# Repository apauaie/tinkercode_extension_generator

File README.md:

**Use these files at your own risk.**

<br>

These files are generator files to create extension zip file for use with Tinkercode apps. It will generate a standard extension with same pin connection as Lekirbot. Please refer to the Lekirbot PCB. 
Content of this github is divided into two:
1. PCB Design with KICAD for LekirBot. It is a simple line following robot with 5 QRE1113 sensors, 2 servo connections, 1 ultrasonic connection, built in TB6612FNG Motor Driver
2. TinkerCode Block Extension Generator to be use with Tinkercode apps from tinkercode.my.

**Instruction to use PCB Files**
PCB files is for KICAD. Free to modify  (Open Source)
Download KICAD to modify these files. https://www.kicad.org/download/

)<br>

)<br>

)<br>

**Instruction to use Extension Generator Files**
Download the files from Github
Place GeneratorBot.exe and lekirbot folder in the same folder.

<br>

Run GeneratorBot.exe to generate extension zip file. Insert your Robot name and Robot Image.

<br>

In Tinkercode Apps, press the Extension (Spanar Icon) button to upload the zip files. 

)<br>

)<br>

Check if your upload is successful by going to the extension menu
)<br>

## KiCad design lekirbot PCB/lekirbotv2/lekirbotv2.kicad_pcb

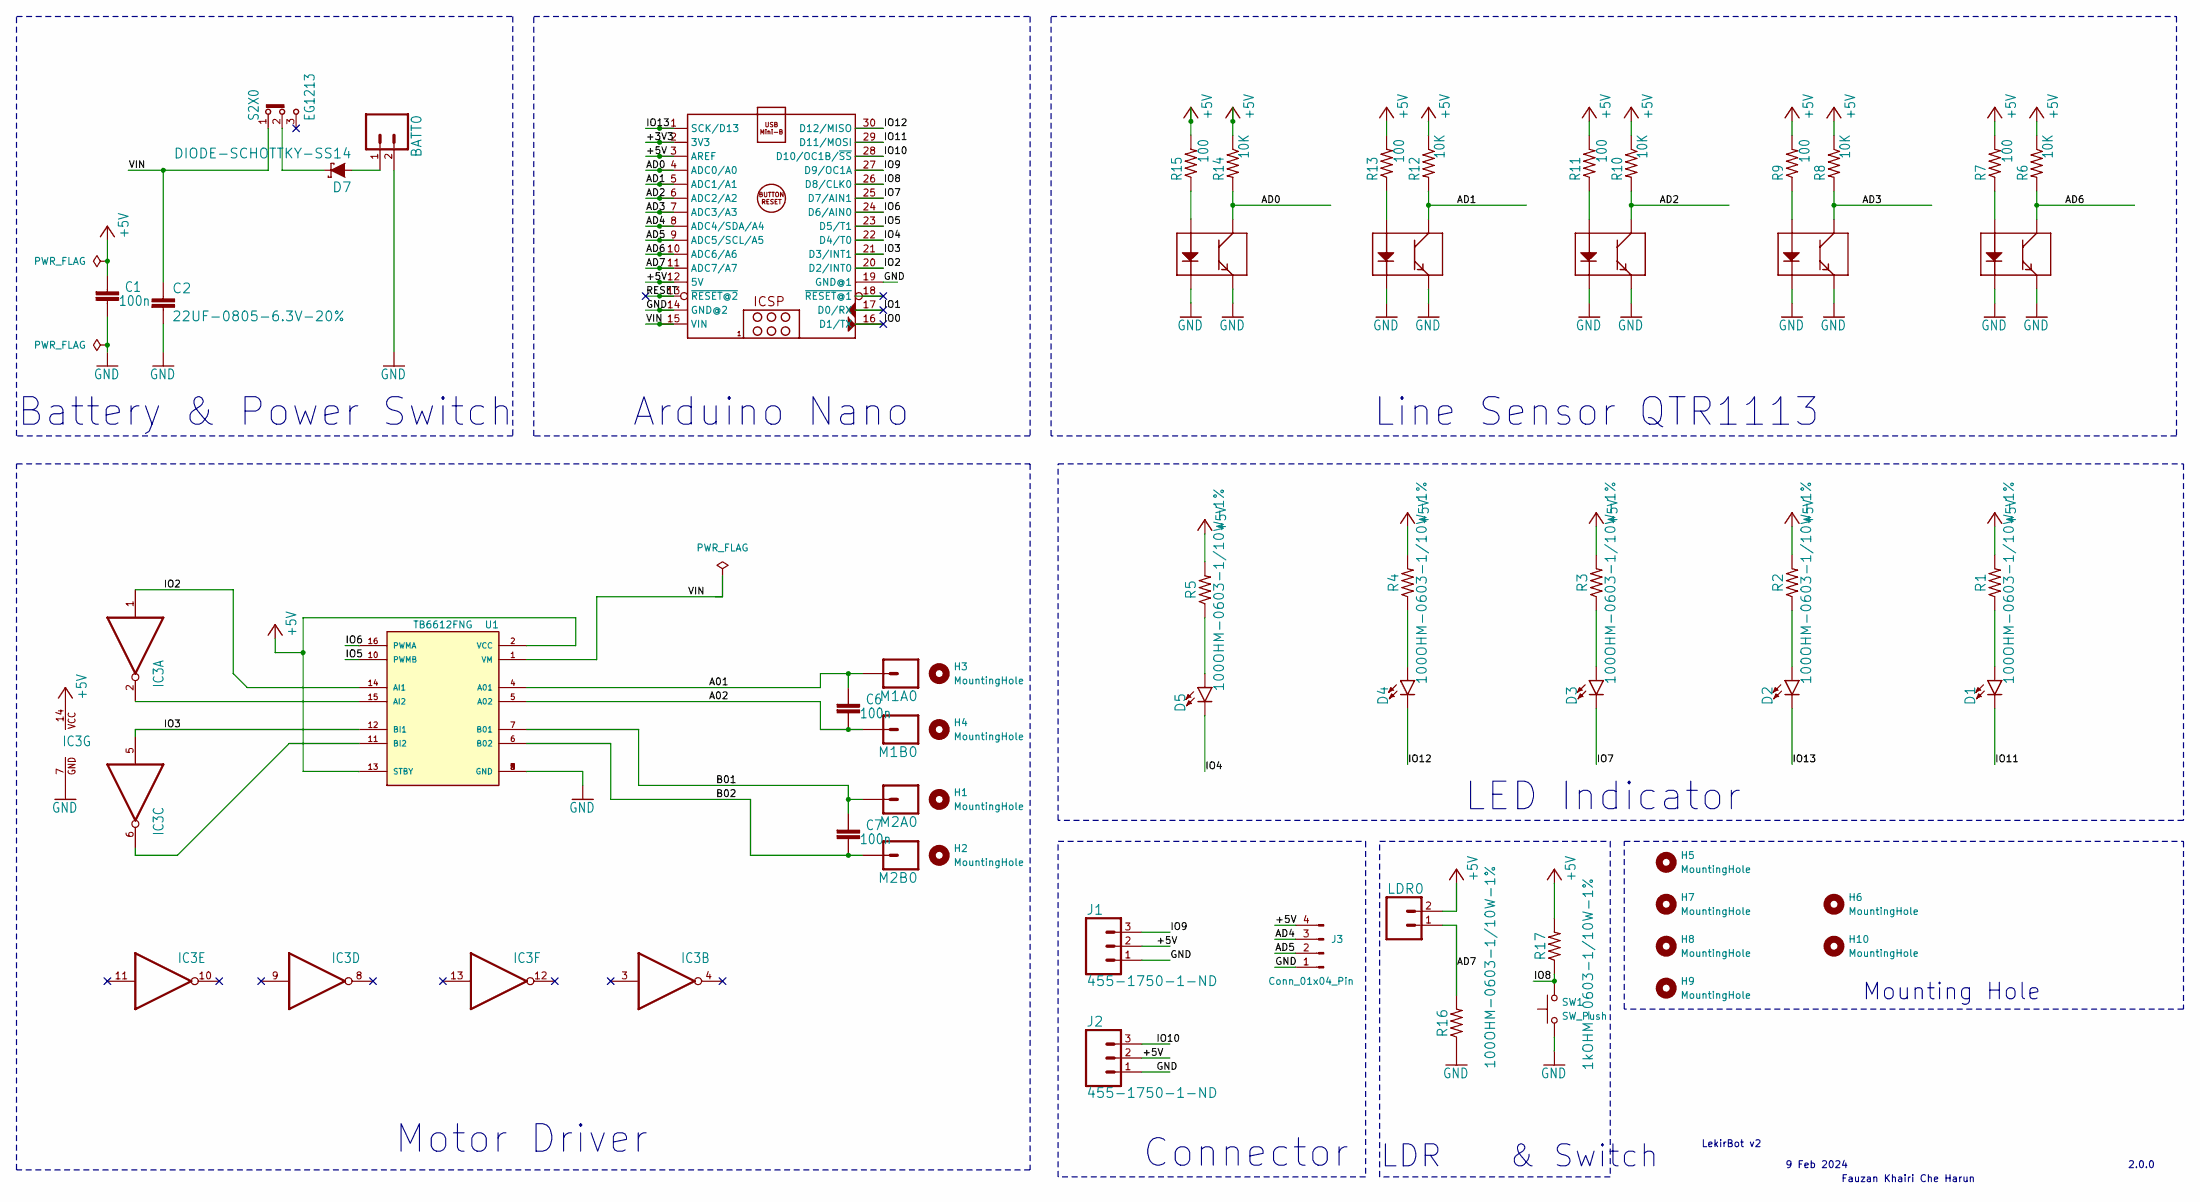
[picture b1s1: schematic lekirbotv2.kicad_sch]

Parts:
ARDUINO_NANO1: ARDUINO_NANO
BATT0: CONN_02; 1X02
C1, C6, C7: 100n; C0603-ROUND
C2: 22UF-0805-6.3V-20%; 0805
D1, D2, D3, D4, D5: LED-FKIT-1206; FKIT-LED-1206
D7: DIODE-SCHOTTKY-SS14; SMA-DIODE
H1, H2, H3, H4, H5, H6, H7, H8, H9, H10: MountingHole; MountingHole_3.2mm_M3
IC3: 7404D; SO14
J1, J2: 455-1750-1-ND; 1X03
J3: Conn_01x04_Pin; PinSocket_1x04_P2.54mm_Vertical
LDR0: CONN_02; 1X02
M1A0, M1B0, M2A0, M2B0: CONN_01; 1X01
R1, R2, R3, R4, R5, R16: 100OHM-0603-1/10W-1%; 0603
R6, R8, R10, R12, R14: 10K; 0603-RES
R7, R9, R11, R13, R15: 100; 0603-RES
R17: 1kOHM-0603-1/10W-1%; 0603
S2X0: EG1213
SW1: SW_Push; SW_PUSH_6mm
U1: TB6612FNG; MODULE_ROB-14450; PARTREV 11-13-17
U2, U5, U6, U7, U8: QRE11131:1; QRE1113-1_1

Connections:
+5V: ARDUINO_NANO1.3 (AREF), ARDUINO_NANO1.12 (5V), C1.2, IC3.14 (VCC), J1.2, J2.2, J3.4, LDR0.2, R1.2, R2.2, R3.2, R4.2, R5.2, R6.1, R7.2, R8.1, R9.2, R10.1, R11.2, R12.1, R13.2, R14.1, R15.2, R17.2, U1.2 (VCC), U1.13 (STBY)
/+3V3: ARDUINO_NANO1.2 (3V3)
/A01: C6.2, M1A0.1, U1.4 (A01)
/A02: C6.1, M1B0.1, U1.5 (A02)
/AD0: ARDUINO_NANO1.4 (ADC0/A0), R14.2, U2.3 (C)
/AD1: ARDUINO_NANO1.5 (ADC1/A1), R12.2, U5.3 (C)
/AD2: ARDUINO_NANO1.6 (ADC2/A2), R10.2, U6.3 (C)
/AD3: ARDUINO_NANO1.7 (ADC3/A3), R8.2, U7.3 (C)
/AD4: ARDUINO_NANO1.8 (ADC4/SDA/A4), J3.3
/AD5: ARDUINO_NANO1.9 (ADC5/SCL/A5), J3.2
/AD6: ARDUINO_NANO1.10 (ADC6/A6), R6.2, U8.3 (C)
/AD7: ARDUINO_NANO1.11 (ADC7/A7), LDR0.1, R16.2
/B01: C7.2, M2A0.1, U1.7 (B01)
/B02: C7.1, M2B0.1, U1.6 (B02)
/IO0: ARDUINO_NANO1.16 (D1/TX)
/IO1: ARDUINO_NANO1.17 (D0/RX)
/IO2: ARDUINO_NANO1.20 (D2/INT0), IC3.1 (I), U1.14 (AI1)
/IO3: ARDUINO_NANO1.21 (D3/INT1), IC3.5 (I), U1.12 (BI1)
/IO4: ARDUINO_NANO1.22 (D4/T0), D5.C
/IO5: ARDUINO_NANO1.23 (D5/T1), U1.10 (PWMB)
/IO6: ARDUINO_NANO1.24 (D6/AIN0), U1.16 (PWMA)
/IO7: ARDUINO_NANO1.25 (D7/AIN1), D3.C
/IO8: ARDUINO_NANO1.26 (D8/CLK0), R17.1, SW1.2
/IO9: ARDUINO_NANO1.27 (D9/OC1A), J1.3
/IO10: ARDUINO_NANO1.28 (D10/OC1B/~SS), J2.3
/IO11: ARDUINO_NANO1.29 (D11/MOSI), D1.C
/IO12: ARDUINO_NANO1.30 (D12/MISO), D4.C
/IO13: ARDUINO_NANO1.1 (SCK/D13), D2.C
/RESET: ARDUINO_NANO1.13 (~RESET@2)
/VIN: ARDUINO_NANO1.15 (VIN), C2.1, S2X0.1, U1.1 (VM)
GND: ARDUINO_NANO1.14 (GND@2), ARDUINO_NANO1.19 (GND@1), BATT0.2, C1.1, C2.2, IC3.7 (GND), J1.1, J2.1, J3.1, R16.1, SW1.1, U1.3 (GND), U1.8 (GND), U1.9 (GND), U2.2 (K), U2.4 (E), U5.2 (K), U5.4 (E), U6.2 (K), U6.4 (E), U7.2 (K), U7.4 (E), U8.2 (K), U8.4 (E)
unnamed: BATT0.1, D7.A
unnamed: D1.A, R1.1
unnamed: D2.A, R2.1
unnamed: D3.A, R3.1
unnamed: D4.A, R4.1
unnamed: D5.A, R5.1
unnamed: D7.C, S2X0.2
unnamed: IC3.2 (O), U1.15 (AI2)
unnamed: IC3.6 (O), U1.11 (BI2)
unnamed: R15.1, U2.1 (A)
unnamed: R13.1, U5.1 (A)
unnamed: R11.1, U6.1 (A)
unnamed: R9.1, U7.1 (A)
unnamed: R7.1, U8.1 (A)

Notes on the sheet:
Arduino Nano
Motor Driver
LDR & Switch
LED Indicator
LekirBot v2
Line Sensor QTR1113
2.0.0
Mounting Hole
Fauzan Khairi Che Harun
9 Feb 2024
Connector
Battery & Power Switch

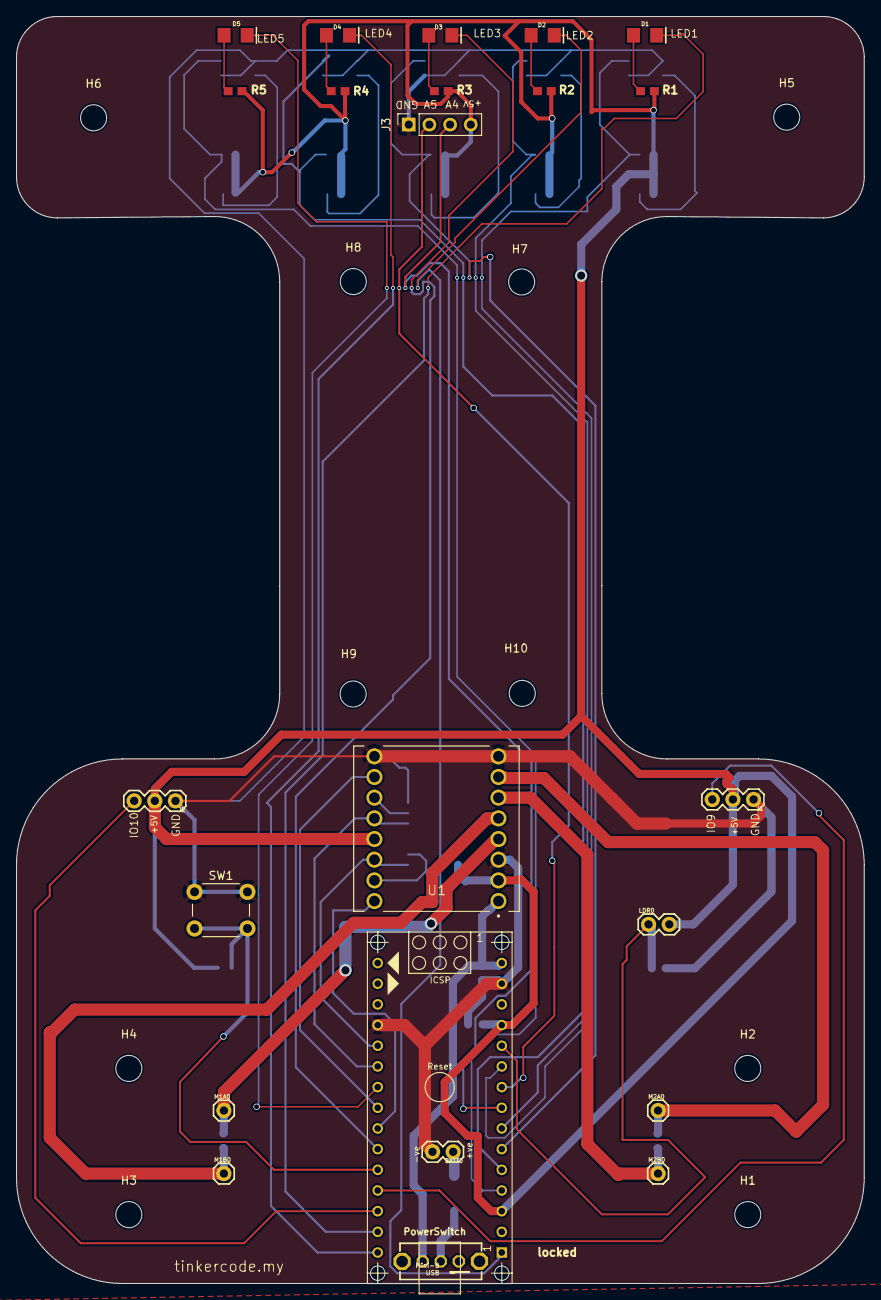
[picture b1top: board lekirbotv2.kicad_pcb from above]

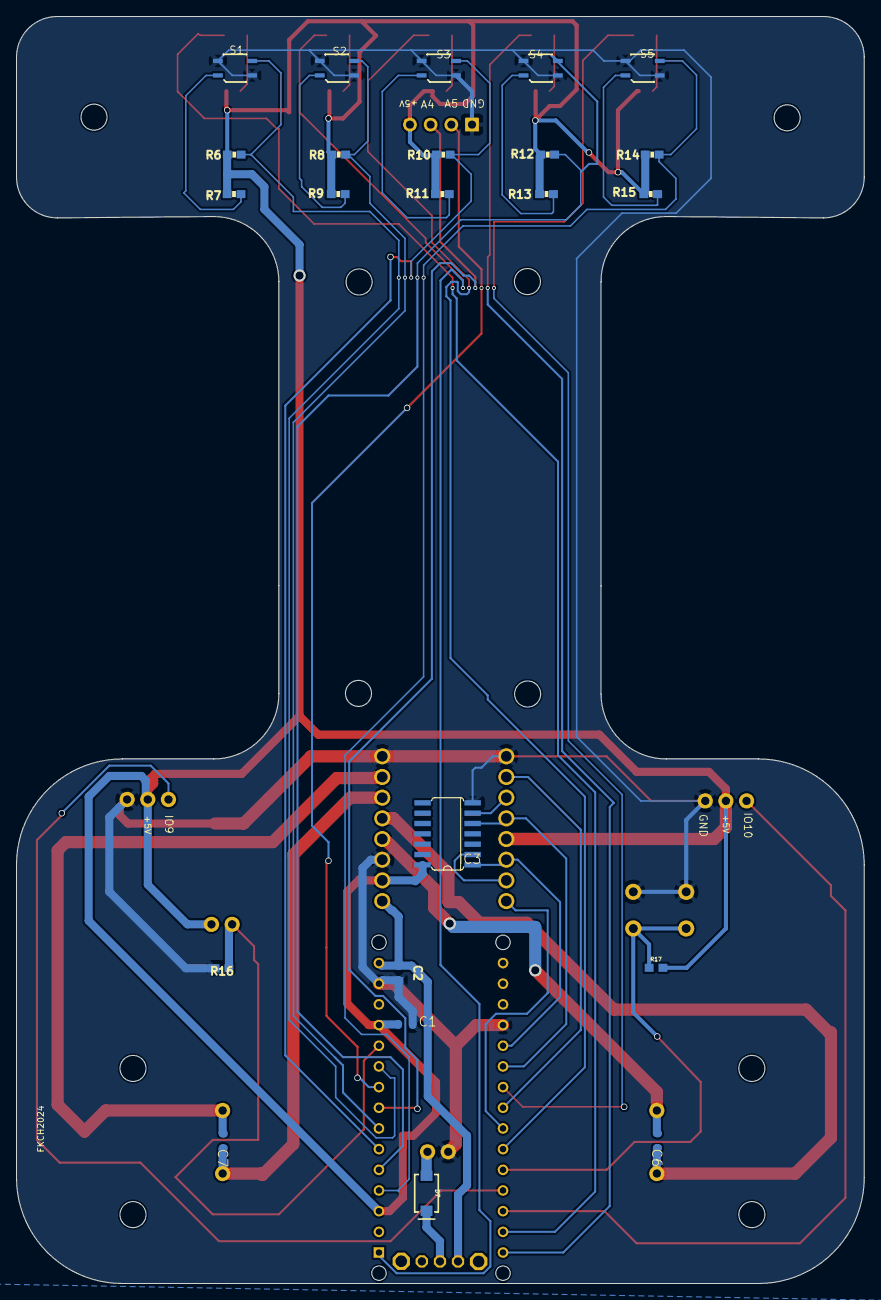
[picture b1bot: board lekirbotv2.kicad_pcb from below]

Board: 2 copper layers, 104.1 x 155.6 mm, 56 parts (23 on the bottom side), 41 nets.

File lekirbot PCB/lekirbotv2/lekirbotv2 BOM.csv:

Comment,Type,Designator,Quantity,Size,Footprint,LCSC,Fabrication Process,Example Link
ARDUINO_NANO 15 Pin Female Connector,Connector,ARDUINO_NANO1,2,2.54 pitch,lekirbot:ARDUINO_NANO,,Soldering,https://shopee.com.my/2P-3P-6P-10P-14P-15P-16P-Pin-Way-2.54m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
CONN_02  2 pin Female,Connector,BATT0,1,2.54 pitch,lekirbot:1X02,,Soldering,https://shopee.com.my/SM-Connector-Wires-2P-2-Pins-(Male)-i.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
LDR,Connector,LDR0,1,,lekirbot:1X02,,Soldering,https://shopee.com.my/Light-Dependent-Resistor-LDR-Sunlight-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
100n,Capacitor,"C1,C6,C7",3,0603,lekirbot:C0603-ROUND,,Soldering,https://shopee.com.my/100PCS-0603-SMD-Chip-Multilayer-Cerami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
22UF-0805-6.3V-20%,Capacitor,C2,1,0805,lekirbot:0805,,Soldering,https://shopee.com.my/100pcs-0805-SMD-Thick-Film-hjxrhgal-Ch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
LED-FKIT-1206,LED,"D1,D2,D3,D4,D5",5,1206,lekirbot:FKIT-LED-1206,,Soldering,https://shopee.com.my/100pcs-0603-0805-1206-3225-1210-smd-le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
DIODE-SCHOTTKY-SS14,Diode,D7,1,SS14,lekirbot:SMA-DIODE,,Soldering,https://shopee.com.my/SS14-SS16-SS24-SS32-SS34-SS36-SS54-SS5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
MountingHole,Hole,"H1,H2,H3,H4,H5,H6,H7,H8,H9,H10",,,MountingHole:MountingHole_3.2mm_M3,,Soldering,
7404D,Inverter,IC3,1,SO14,lekirbot:SO14,,Soldering,https://shopee.com.my/20PCS-74HC04D-SOP14-74HC04-SOP-SN74HC0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
CONN_3 3 pin Female,Connector,"J1,J2",2,2.54 pitch,lekirbot:1X03,,Soldering,https://shopee.com.my/2P-3P-6P-10P-14P-15P-16P-Pin-Way-2.54m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
Conn_04 4 pin Female,Connector,J3,1,2.54 pitch,Connector_PinSocket_2.54mm:PinSocket_1x04_P2.54mm_Vertical,,Soldering,https://shopee.com.my/2P-3P-6P-10P-14P-15P-16P-Pin-Way-2.54m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
CONN_01 1 pin Female,Connector,"M1A0,M1B0,M2A0,M2B0",4,,lekirbot:1X01,,Soldering,https://shopee.com.my/20-Pin-2.54-mm-Single-Row-Pin-Male-Hea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
100OHM-0603-1/10W-1%,Resistor,"R1,R2,R3,R4,R5,R16",6,0603,lekirbot:0603,,Soldering,https://shopee.com.my/36values*20pcs-720pcs-0603-1ohm-10Mohm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
1kOHM-0603-1/10W-1%,Resistor,R17,1,0603,lekirbot:0603,,Soldering,https://shopee.com.my/36values*20pcs-720pcs-0603-1ohm-10Mohm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
10KOHM-0603,Resistor,"R6,R8,R10,R12,R14",5,0603,lekirbot:0603-RES,,Soldering,https://shopee.com.my/36values*20pcs-720pcs-0603-1ohm-10Mohm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
100OHM-0603-0.25W-1%,Resistor,"R7,R9,R11,R13,R15",5,0603,lekirbot:0603-RES,,Soldering,https://shopee.com.my/36values*20pcs-720pcs-0603-1ohm-10Mohm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
EG1213,Switch Slide,S2X0,1,EG1213,lekirbot:EG1213,,Soldering,https://shopee.com.my/1pcs-Horizontal-5Pin-Slide-Switch-SPDT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
SW_Push,Switch Push,SW1,1,6mmx6mm,Button_Switch_THT:SW_PUSH_6mm,,Soldering,https://shopee.com.my/6x6x5mm-Push-Button-i.8822702.15541537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
TB6612FNG,Motor Driver IC,U1,1,,ROB-14450:MODULE_ROB-14450,,Soldering,https://shopee.com.my/TB6612-DRV8833-Dual-Motor-Driver-1A-TB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
QRE11131:1,Infrared Sensor,"U2,U5,U6,U7,U8",5,,lekirbot:QRE1113-1_1,,Soldering,https://shopee.com.my/10pcs-lot-QRE1113GR-QRE1113-QRE1113G-S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
N20 Motor,Motor,,2,,,,Assembly,https://shopee.com.my/GA12-N20-300-Geared-Motor-Rubber-Wheel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
N20 Motor Bracket,Bracket,,2,,,,Assembly,https://shopee.com.my/GA12-N20-300-Geared-Motor-Rubber-Wheel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
Wheel,Wheel,,2,,,,Assembly,https://shopee.com.my/GA12-N20-300-Geared-Motor-Rubber-Wheel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
Arduino Nano,Arduino Nano,,1,,,,Assembly,https://shopee.com.my/ATmega328P-Nano-Compatible-CH340-USB-M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
7.4V Battery Lipo,Battery,,1,,,,Assembly,https://shopee.com.my/Li-on-2s-7.4V-3000mAh-18650-Battery-Li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
Lipo Battery Charger,Battery,,1,,,,Assembly,https://shopee.com.my/Li-on-2s-7.4V-3000mAh-18650-Battery-Li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
USB Cable Programming,Cable,,1,,,,Assembly,https://shopee.com.my/ATmega328P-Nano-Compatible-CH340-USB-M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

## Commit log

2024-02-05 Update Exe Pyinstaller files
2024-02-05 Media update
2024-02-05 Update Media
2024-02-05 ignore DS
2024-02-08 Update lekirbot v2
2024-02-08 Update v2
2024-02-09 Updated lekirbotv2
2024-02-26 Update lekirbot
2024-02-27 Fix variable in h
2024-02-27 update color
2024-03-04 Update 3d model
2024-03-05 updated 3d component lekirbot2
2024-03-12 Upload ESP32 Extension
2024-03-12 include esp32 jebatbot selection
2024-03-12 auto backup
2024-03-12 update geneartebot.exe for jebatbot
2024-03-12 updated lekirbotv2 production file
2024-03-12 auto
2024-03-12 update jebat mini xml
2024-03-13 update sens for jebatbot
2024-03-15 update rgb for jebatbot
2024-03-24 Updte LCSC component
